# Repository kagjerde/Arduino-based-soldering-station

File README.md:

# Arduino-soldering-station
This is a soldering station using Weller RT soldering tips. <br/><br/>
- The project files contains 3D model for the housing and a PCB board using Arduino Nano microcontroller.<br/>
- Source code is written i C, and uses PID library for temperature control.<br/>
- PCB files are generated in KiCad, and include Gerber files.<br/>
- The project uses Arduino Nano board for the microcontroller.<br/>
<br/>

<br/>

This project is based on [ConnyCola](https://github.com/ConnyCola/SolderingStation/tree/master/3D)'s soldering station, but uses a modified source code and 3D model.

The display show the following information:

The display will change colour from Cyan, Yellow, and Green dependent on the difference between SET and ACTual temperature. 
<br/>
The SET point will be set to 20 degrees if the soldering tip it placed in the holder, or the selector button is pressed once - Standby mode.<br/>
At the bottom right of the screen, a small bar shows the PWM output in %. 
<br/><br/><br/>

The display will show the temperature curve, repeating approx. every 20 seconds. To enter the Graph mode, the selector switch has to pressed for more than 1 second.

At the bottom left a small dot is showing if the soldering station is in Standby mode.

## PCB

<br/><br/><br/><br/><br/><br/><br/><br/><br/>

## Cirquit diagram

## Credits

The Weller RT product is a trademark of [Weller Tools GmbH](https://www.weller-tools.com/index.html)

The original project is written by [ConnyCola](https://github.com/ConnyCola/SolderingStation/tree/master/3D)

## License

The MIT License (MIT)

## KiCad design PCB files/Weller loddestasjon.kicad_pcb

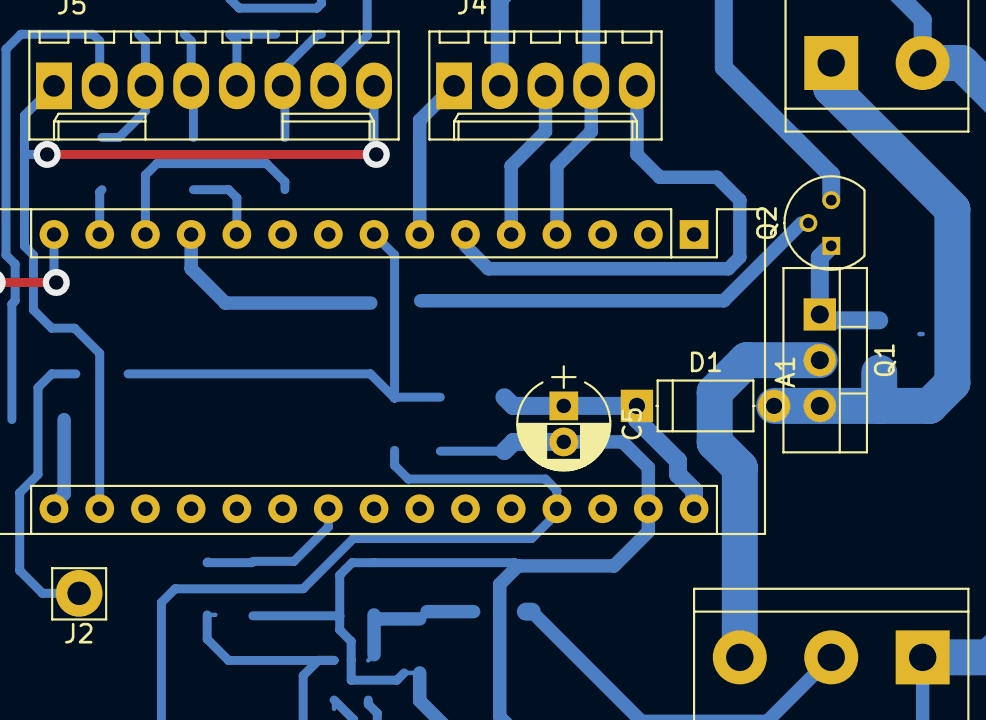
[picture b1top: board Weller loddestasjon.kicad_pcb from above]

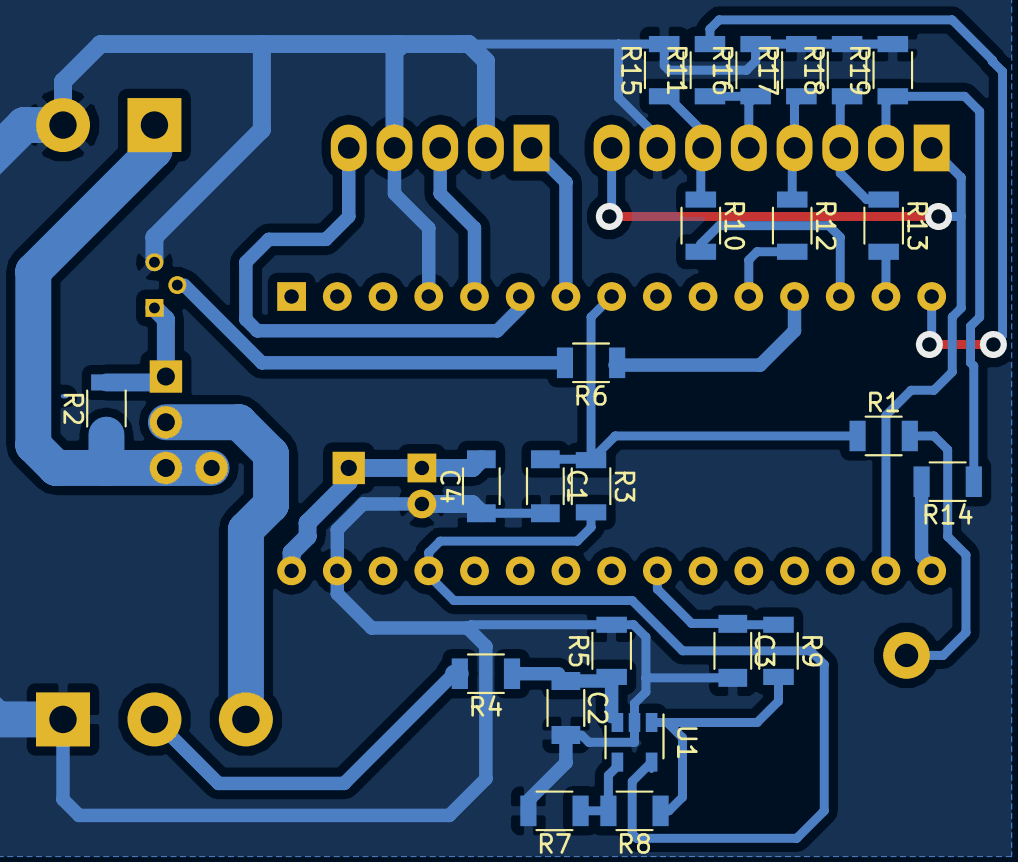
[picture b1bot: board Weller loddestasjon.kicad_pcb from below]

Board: 2 copper layers, 34 parts (24 on the bottom side), 29 nets.

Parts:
A1: Arduino_Nano_v3.x; Arduino_Nano
C1, C2, C3, C4: C; C_1206
C5: CP; CP_Radial_D5.0mm_P2.00mm
D1: D; D_A-405_P7.62mm_Horizontal
J1: Screw_Terminal_01x03; TerminalBlock_bornier-3_P5.08mm
J2: Conn_01x01; Pin_d1.3mm_L11.3mm_W2.8mm_Flat
J3: Screw_Terminal_01x02; TerminalBlock_bornier-2_P5.08mm
J4: Conn_01x05; Molex_KK-6410-05_05x2.54mm_Straight
J5: Conn_01x08; Molex_KK-6410-08_08x2.54mm_Straight
Q1: IRF9540N; TO-220-3_Vertical
Q2: BC547; TO-92_Molded_Narrow
R1, R2, R3, R4, R5, R6, R7, R8, R9, R10, R11, R12, R13, R14, R15, R16, R17, R18, R19: R; R_1206
U1: OPA333xxDBV; SOT-23-5

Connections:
+3V3: A1.17, J5.1, J5.8
+12V: D1.2, J3.1, Q1.3, R2.1
A: A1.5, J4.3
A0: A1.11, R12.2
B: A1.6, J4.5
CS: A1.13, R10.2
GND: A1.4, A1.29, C1.2, C2.2, C3.2, C4.1, C5.2, J1.1, J3.2, J4.2, J4.4, J5.7, Q2.3, R5.2, R7.2, R15.2, R16.2, R17.2, R18.2, R19.2, U1.2
unnamed: A1.30, C4.2, C5.1, D1.1
unnamed: C2.1, R4.1, R5.1, U1.3
unnamed: J1.2, R4.2
unnamed: J1.3, Q1.2
unnamed: J2.1, R1.2
unnamed: J5.2, R14.1, R19.1
unnamed: J5.3, R13.1, R18.1
unnamed: J5.4, R12.1, R17.1
unnamed: J5.5, R11.1, R16.1
unnamed: J5.6, R10.1, R15.1
unnamed: Q1.1, Q2.1, R2.2
unnamed: Q2.2, R6.2
unnamed: R7.1, R8.2, U1.4
unnamed: R8.1, R9.2, U1.1
PWM: A1.12, R6.1
RESET: A1.15, R11.2
SCK: A1.16, R14.2
SDA: A1.14, R13.2
SENSE: A1.8, C1.1, R1.1, R3.1
SW: A1.7, J4.1
Temp: A1.22, C3.1, R9.1
VCC: A1.27, R3.2, U1.5

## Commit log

2025-05-26 Add files via upload
    The design is compatible with Weller RTxx type soldering tips.
